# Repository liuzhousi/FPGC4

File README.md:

# FPGC4

[Project Wiki](https://www.b4rt.nl/fpgc4/)

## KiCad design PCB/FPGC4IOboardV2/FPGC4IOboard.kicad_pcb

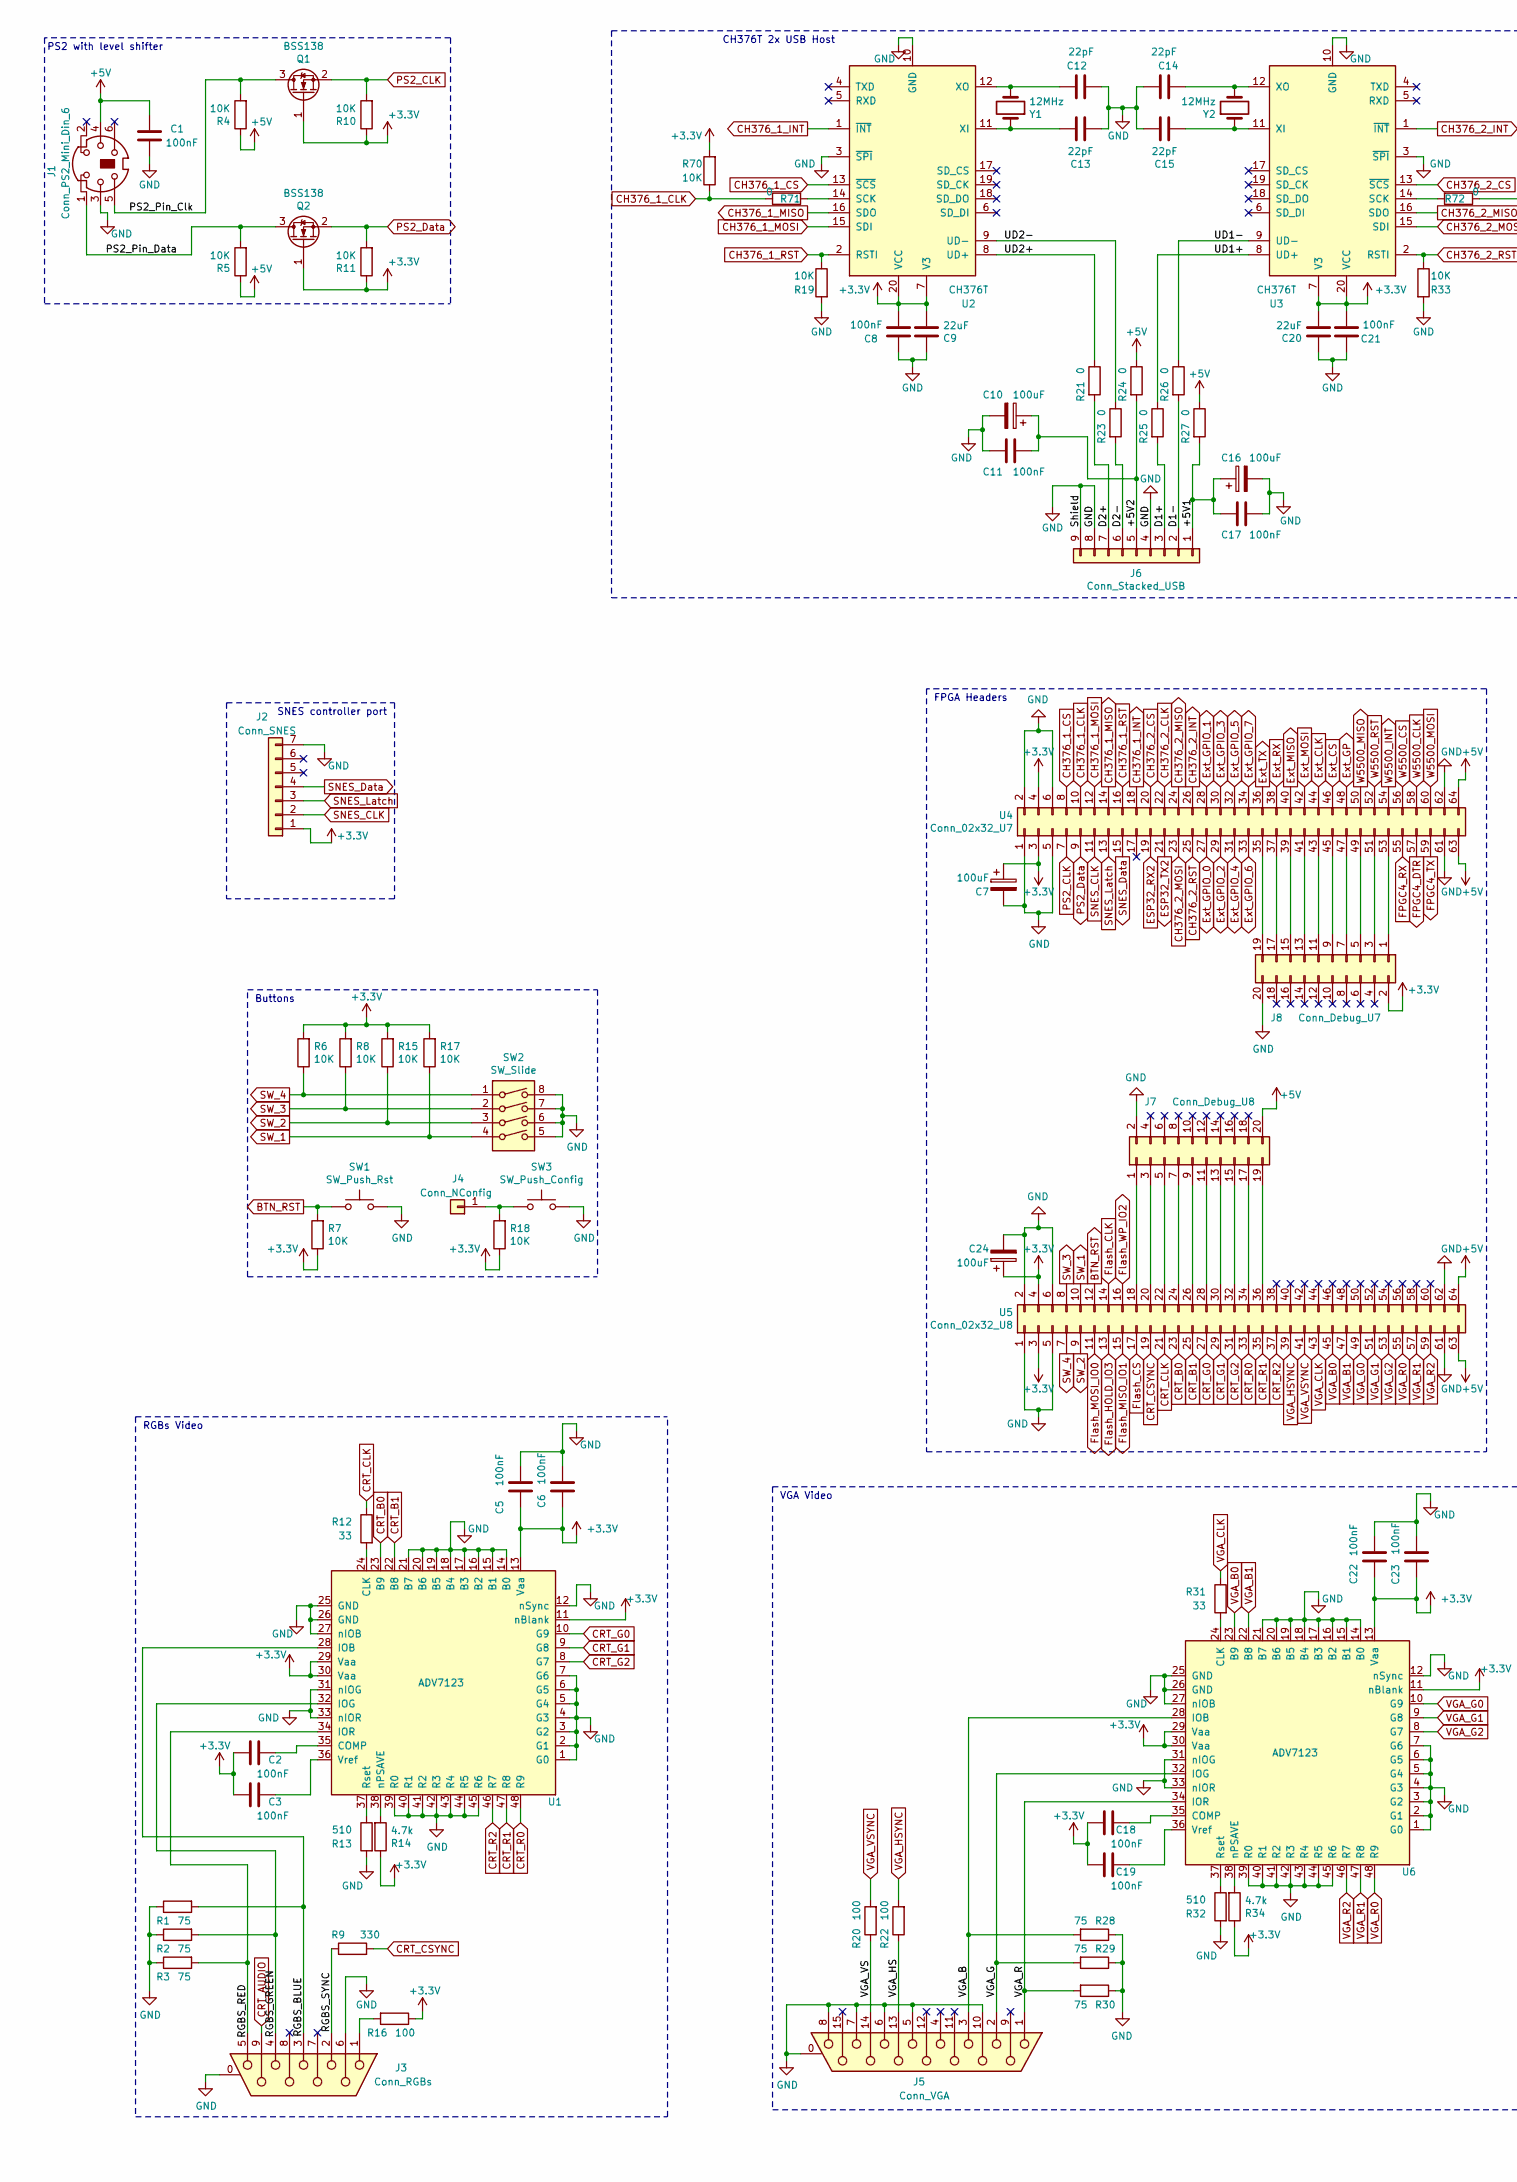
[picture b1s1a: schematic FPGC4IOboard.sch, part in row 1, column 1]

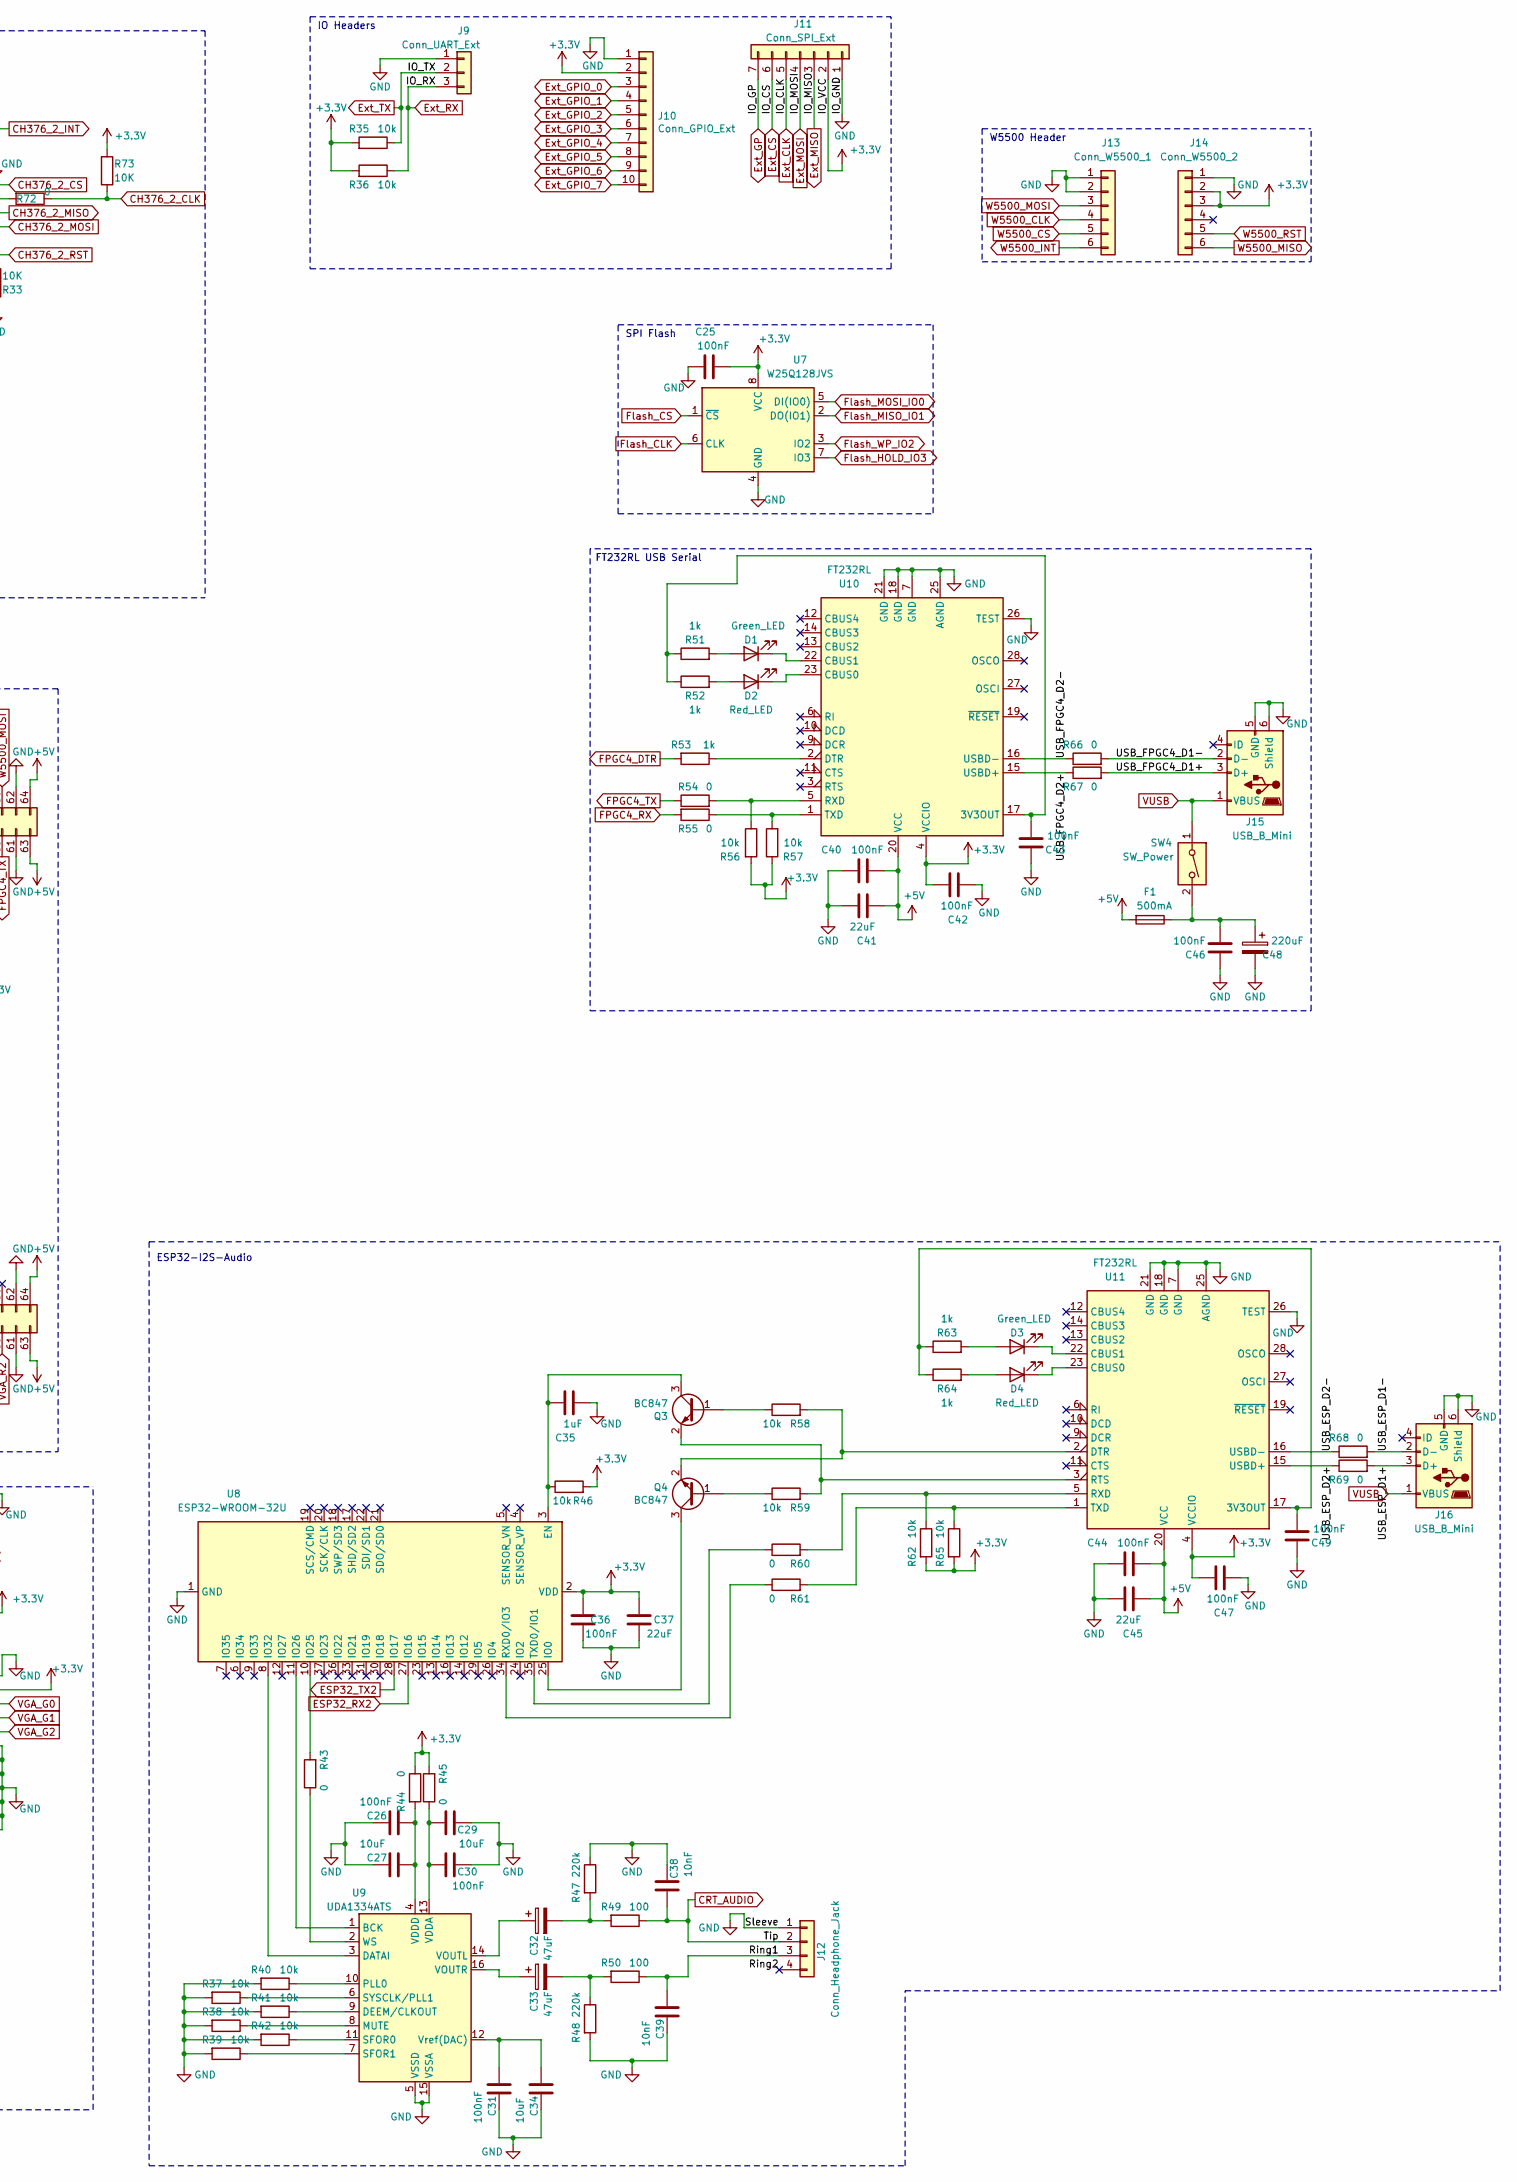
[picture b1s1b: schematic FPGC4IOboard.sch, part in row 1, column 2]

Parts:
C1, C2, C3, C5, C6, C8, C11, C17, C18, C19, C21, C22, C23, C25, C26, C30, C31, C36, C40, C42, C43, C44, C46, C47, C49: 100nF; C_0805_2012Metric_Pad1.15x1.40mm_HandSolder
C7, C10, C16, C24: 100uF; CP_Radial_D4.0mm_P2.00mm
C9, C20, C37, C41, C45: 22uF; C_0805_2012Metric_Pad1.15x1.40mm_HandSolder
C12, C13, C14, C15: 22pF; C_0805_2012Metric_Pad1.15x1.40mm_HandSolder
C27, C29, C34: 10uF; C_0805_2012Metric_Pad1.15x1.40mm_HandSolder
C32, C33: 47uF; CP_Radial_D4.0mm_P2.00mm
C35: 1uF; C_0805_2012Metric_Pad1.15x1.40mm_HandSolder
C38, C39: 10nF; C_0805_2012Metric_Pad1.15x1.40mm_HandSolder
C48: 220uF; CP_Radial_D5.0mm_P2.00mm
D1, D3: Green_LED; LED_0805_2012Metric_Pad1.15x1.40mm_HandSolder
D2, D4: Red_LED; LED_0805_2012Metric_Pad1.15x1.40mm_HandSolder
F1: 500mA; Fuse_1812_4532Metric_Pad1.30x3.40mm_HandSolder
J1: Conn_PS2_Mini_Din_6; Connector_Mini-DIN_Female_6Pin_2rows
J2: Conn_SNES; SNES_controller_port
J3: Conn_RGBs; DSUB9_CRT
J4: Conn_NConfig; PinHeader_1x01_P2.54mm_Vertical
J5: Conn_VGA; VGA_EDAC
J6: Conn_Stacked_USB; USB_A_Wuerth_61400826021_Horizontal_Stacked
J7: Conn_Debug_U8; PinHeader_2x10_P2.54mm_Vertical
J8: Conn_Debug_U7; PinHeader_2x10_P2.54mm_Vertical
J9: Conn_UART_Ext; PinSocket_1x03_P2.54mm_Vertical
J10: Conn_GPIO_Ext; PinSocket_1x10_P2.54mm_Vertical
J11: Conn_SPI_Ext; PinSocket_1x07_P2.54mm_Vertical
J12: Conn_Headphone_Jack; TRRS-PJ-320A
J13: Conn_W5500_1; PinSocket_1x06_P2.54mm_Vertical
J14: Conn_W5500_2; PinSocket_1x06_P2.54mm_Vertical
J15, J16: USB_B_Mini; USB_Mini-B_Lumberg_2486_01_Horizontal
Q1, Q2: BSS138; SOT-23
Q3, Q4: BC847; SOT-23
R1, R2, R3, R28, R29, R30: 75; R_0805_2012Metric_Pad1.15x1.40mm_HandSolder
R4, R5, R6, R7, R8, R10, R11, R15, R17, R18, R19, R33, R70, R73: 10K; R_0805_2012Metric_Pad1.15x1.40mm_HandSolder
R9: 330; R_0805_2012Metric_Pad1.15x1.40mm_HandSolder
R12, R31: 33; R_0805_2012Metric_Pad1.15x1.40mm_HandSolder
R13, R32: 510; R_0805_2012Metric_Pad1.15x1.40mm_HandSolder
R14, R34: 4.7k; R_0805_2012Metric_Pad1.15x1.40mm_HandSolder
R16, R20, R22, R49, R50: 100; R_0805_2012Metric_Pad1.15x1.40mm_HandSolder
R21, R23, R24, R25, R26, R27, R43, R44, R45, R54, R55, R60, R61, R66, R67, R68, R69, R71, R72: 0; R_0805_2012Metric_Pad1.15x1.40mm_HandSolder
R35, R36, R37, R38, R39, R40, R41, R42, R46, R56, R57, R58, R59, R62, R65: 10k; R_0805_2012Metric_Pad1.15x1.40mm_HandSolder
R47, R48: 220k; R_0805_2012Metric_Pad1.15x1.40mm_HandSolder
R51, R52, R53, R63, R64: 1k; R_0805_2012Metric_Pad1.15x1.40mm_HandSolder
SW1: SW_Push_Rst; SW_Tactile_SPST_Angled_PTS645Vx39-2LFS
SW2: SW_Slide; SW_DIP_SPSTx04_Slide_6.7x11.72mm_W8.61mm_P2.54mm_LowProfile
SW3: SW_Push_Config; SW_Tactile_SPST_Angled_PTS645Vx39-2LFS
SW4: SW_Power; switchAngled
U1, U6: ADV7123; LQFP-48_7x7mm_P0.5mm
U2, U3: CH376T; SSOP-20_5.3x7.2mm_P0.65mm
U4: Conn_02x32_U7; PinHeader_2x32_P2.54mm_Vertical
U5: Conn_02x32_U8; PinHeader_2x32_P2.54mm_Vertical
U7: W25Q128JVS; SOIC-8_5.23x5.23mm_P1.27mm
U8: ESP32-WROOM-32U
U9: UDA1334ATS; SSOP-16_4.4x5.2mm_P0.65mm
U10, U11: FT232RL; SSOP-28_5.3x10.2mm_P0.65mm
Y1, Y2: 12MHz; Crystal_HC49-4H_Vertical

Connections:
+3V3: C2.1, C3.1, C5.2, C6.1, C7.1, C8.2, C9.2, C18.1, C19.1, C20.2, C21.2, C22.2, C23.1, C24.1, C25.2, C36.2, C37.2, C42.2, C47.2, J2.1, J8.2, J10.2, J11.2, J14.2, J14.3, Q1.1 (G), Q2.1 (G), R6.2, R7.1, R8.2, R10.1, R11.1, R14.1, R15.2, R16.1, R17.2, R18.1, R34.1, R35.2, R36.2, R44.1, R45.2, R46.2, R56.2, R57.1, R62.2, R65.2, R70.2, R73.2, U1.11 (nBlank), U1.13 (Vaa), U1.29 (Vaa), U1.30 (Vaa), U2.7 (V3), U2.20 (VCC), U3.7 (V3), U3.20 (VCC), U4.3, U4.4, U5.3, U5.4, U6.11 (nBlank), U6.13 (Vaa), U6.29 (Vaa), U6.30 (Vaa), U7.8 (VCC), U8.2 (VDD), U10.4 (VCCIO), U11.4 (VCCIO)
+5V: C1.1, C40.2, C41.1, C44.2, C45.1, F1.2, J1.4, J7.20, R4.1, R5.1, R24.1, R27.1, U4.63, U4.64, U5.63, U5.64, U10.20 (VCC), U11.20 (VCC)
/+5V1: C16.1, C17.2, J6.1, R27.2
/+5V2: C10.1, C11.2, J6.5, R24.2
/D1+: J6.3, R25.2
/D1-: J6.2, R26.2
/D2+: J6.7, R21.2
/D2-: J6.6, R23.2
/PS2_Pin_Clk: J1.5, Q1.3 (D), R4.2
/PS2_Pin_Data: J1.1, Q2.3 (D), R5.2
/RGBS_BLUE: J3.3, R1.2, U1.28 (IOB)
/RGBS_GREEN: J3.4, R2.2, U1.32 (IOG)
/RGBS_RED: J3.5, R3.2, U1.34 (IOR)
/RGBS_SYNC: J3.2, R9.1
/Ring1: C39.1, J12.3, R50.1
/Ring2: J12.4
/UD1+: R25.1, U3.8 (UD+)
/UD1-: R26.1, U3.9 (UD-)
/UD2+: R21.1, U2.8 (UD+)
/UD2-: R23.1, U2.9 (UD-)
/USB_ESP_D1+: J16.3 (D+), R69.2
/USB_ESP_D1-: J16.2 (D-), R68.2
/USB_ESP_D2+: R69.1, U11.15 (USBD+)
/USB_ESP_D2-: R68.1, U11.16 (USBD-)
/USB_FPGC4_D1+: J15.3 (D+), R67.2
/USB_FPGC4_D1-: J15.2 (D-), R66.2
/USB_FPGC4_D2+: R67.1, U10.15 (USBD+)
/USB_FPGC4_D2-: R66.1, U10.16 (USBD-)
/VGA_B: J5.3, R28.2, U6.28 (IOB)
/VGA_G: J5.2, R29.2, U6.32 (IOG)
/VGA_HS: J5.13, R22.1
/VGA_R: J5.1, R30.2, U6.34 (IOR)
/VGA_VS: J5.14, R20.1
BTN_RST: R7.2, SW1.1, U5.12
CH376_1_CLK: R70.1, R71.1, U4.10
CH376_1_CS: U2.13 (~SCS), U4.8
CH376_1_INT: U2.1 (~INT~), U4.18
CH376_1_MISO: U2.16 (SDO), U4.14
CH376_1_MOSI: U2.15 (SDI), U4.12
CH376_1_RST: R19.1, U2.2 (RSTI), U4.16
CH376_2_CLK: R72.1, R73.1, U4.22
CH376_2_CS: U3.13 (~SCS), U4.20
CH376_2_INT: U3.1 (~INT~), U4.26
CH376_2_MISO: U3.16 (SDO), U4.24
CH376_2_MOSI: U3.15 (SDI), U4.23
CH376_2_RST: R33.1, U3.2 (RSTI), U4.25
CRT_AUDIO: C38.1, J3.9, J12.2, R49.1
CRT_B0: U1.23 (B9), U5.23
CRT_B1: U1.22 (B8), U5.25
CRT_CLK: R12.1, U5.21
CRT_CSYNC: R9.2, U5.19
CRT_G0: U1.10 (G9), U5.27
CRT_G1: U1.9 (G8), U5.29
CRT_G2: U1.8 (G7), U5.31
CRT_R0: U1.48 (R9), U5.33
CRT_R1: U1.47 (R8), U5.35
CRT_R2: U1.46 (R7), U5.37
ESP32_RX2: U4.19, U8.27 (IO16)
ESP32_TX2: U4.21, U8.28 (IO17)
Ext_CLK: J11.5, U4.44
Ext_CS: J11.6, U4.46
Ext_GP: J11.7, U4.48
Ext_GPIO_0: J10.3, U4.27
Ext_GPIO_1: J10.4, U4.28
Ext_GPIO_2: J10.5, U4.29
Ext_GPIO_3: J10.6, U4.30
Ext_GPIO_4: J10.7, U4.31
Ext_GPIO_5: J10.8, U4.32
Ext_GPIO_6: J10.9, U4.33
Ext_GPIO_7: J10.10, U4.34
Ext_MISO: J11.3, U4.40
Ext_MOSI: J11.4, U4.42
Ext_RX: J9.3, R36.1, U4.38
Ext_TX: J9.2, R35.1, U4.36
FPGC4_DTR: R53.2, U4.57
FPGC4_RX: R55.2, U4.55
FPGC4_TX: R54.1, U4.59
Flash_CLK: U5.14, U7.6 (CLK)
Flash_CS: U5.17, U7.1 (~CS)
Flash_HOLD_IO3: U5.13, U7.7 (IO3)
Flash_MISO_IO1: U5.15, U7.2 (DO(IO1))
Flash_MOSI_IO0: U5.11, U7.5 (DI(IO0))
Flash_WP_IO2: U5.16, U7.3 (IO2)
GND: C1.2, C5.1, C6.2, C7.2, C8.1, C9.1, C10.2, C11.1, C12.2, C13.1, C14.2, C15.1, C16.2, C17.1, C20.1, C21.1, C22.1, C23.2, C24.2, C25.1, C26.2, C27.2, C29.2, C30.2, C31.2, C34.2, C35.2, C36.1, C37.1, C38.2, C39.2, C40.1, C41.2, C42.1, C43.1, C44.1, C45.2, C46.1, C47.1, C48.2, C49.1, J1.3, J2.7, J3.0 (PAD), J3.6, J5.0 (PAD), J5.5, J5.6, J5.7, J5.8, J5.10, J6.4, J6.8, J6.9, J7.2, J8.20, J9.1, J10.1, J11.1, J12.1, J13.1, J13.2, J14.1, J15.5 (GND), J15.6 (Shield), J16.5 (GND), J16.6 (Shield), R1.1, R2.1, R3.1, R13.2, R19.2, R28.1, R29.1, R30.1, R32.2, R33.2, R37.2, R38.2, R39.2, R40.2, R41.2, R42.2, R47.1, R48.2, SW1.2, SW2.5, SW2.6, SW2.7, SW2.8, SW3.2, U1.1 (G0), U1.2 (G1), U1.3 (G2), U1.4 (G3), U1.5 (G4), U1.6 (G5), U1.7 (G6), U1.12 (nSync), U1.14 (B0), U1.15 (B1), U1.16 (B2), U1.17 (B3), U1.18 (B4), U1.19 (B5), U1.20 (B6), U1.21 (B7), U1.25 (GND), U1.26 (GND), U1.27 (nIOB), U1.31 (nIOG), U1.33 (nIOR), U1.39 (R0), U1.40 (R1), U1.41 (R2), U1.42 (R3), U1.43 (R4), U1.44 (R5), U1.45 (R6), U2.3 (~SPI~), U2.10 (GND), U3.3 (~SPI~), U3.10 (GND), U4.1, U4.2, U4.5, U4.6, U4.61, U4.62, U5.1, U5.2, U5.5, U5.6, U5.61, U5.62, U6.1 (G0), U6.2 (G1), U6.3 (G2), U6.4 (G3), U6.5 (G4), U6.6 (G5), U6.7 (G6), U6.12 (nSync), U6.14 (B0), U6.15 (B1), U6.16 (B2), U6.17 (B3), U6.18 (B4), U6.19 (B5), U6.20 (B6), U6.21 (B7), U6.25 (GND), U6.26 (GND), U6.27 (nIOB), U6.31 (nIOG), U6.33 (nIOR), U6.39 (R0), U6.40 (R1), U6.41 (R2), U6.42 (R3), U6.43 (R4), U6.44 (R5), U6.45 (R6), U7.4 (GND), U8.1 (GND), U8.15 (GND), U8.38 (GND), U8.39 (GND), U9.5 (VSSD), U9.15 (VSSA), U10.7 (GND), U10.18 (GND), U10.21 (GND), U10.25 (AGND), U10.26 (TEST), U11.7 (GND), U11.18 (GND), U11.21 (GND), U11.25 (AGND), U11.26 (TEST)
unnamed: C2.2, U1.35 (COMP)
unnamed: C3.2, U1.36 (Vref)
unnamed: C12.1, U2.12 (XO), Y1.2
unnamed: C13.2, U2.11 (XI), Y1.1
unnamed: C14.1, U3.12 (XO), Y2.2
unnamed: C15.2, U3.11 (XI), Y2.1
unnamed: C18.2, U6.35 (COMP)
unnamed: C19.2, U6.36 (Vref)
unnamed: C26.1, C27.1, R44.2, U9.4 (VDDD)
unnamed: C29.1, C30.1, R45.1, U9.13 (VDDA)
unnamed: C31.1, C34.1, U9.12 (Vref(DAC))
unnamed: C32.1, U9.14 (VOUTL)
unnamed: C32.2, R47.2, R49.2
unnamed: C33.1, U9.16 (VOUTR)
unnamed: C33.2, R48.1, R50.2
unnamed: C35.1, Q3.3 (C), R46.1, U8.3 (EN)
unnamed: C43.2, R51.1, R52.1, U10.17 (3V3OUT)
unnamed: C46.2, C48.1, F1.1, SW4.2
unnamed: C49.2, R63.1, R64.1, U11.17 (3V3OUT)
unnamed: D1.1 (K), U10.22 (CBUS1)
unnamed: D1.2 (A), R51.2
unnamed: D2.1 (K), U10.23 (CBUS0)
unnamed: D2.2 (A), R52.2
unnamed: D3.1 (K), U11.22 (CBUS1)
unnamed: D3.2 (A), R63.2
unnamed: D4.1 (K), U11.23 (CBUS0)
unnamed: D4.2 (A), R64.2
unnamed: J3.1, R16.2
unnamed: J4.1, R18.2, SW3.1
unnamed: J7.1, U5.18
unnamed: J7.3, U5.20
unnamed: J7.5, U5.22
unnamed: J7.7, U5.24
unnamed: J7.9, U5.26
unnamed: J7.11, U5.28
unnamed: J7.13, U5.30
unnamed: J7.15, U5.32
unnamed: J7.17, U5.34
unnamed: J7.19, U5.36
unnamed: J8.1, U4.53
unnamed: J8.3, U4.51
unnamed: J8.5, U4.49
unnamed: J8.7, U4.47
unnamed: J8.9, U4.45
unnamed: J8.11, U4.43
unnamed: J8.13, U4.41
unnamed: J8.15, U4.39
unnamed: J8.17, U4.37
unnamed: J8.19, U4.35
unnamed: Q3.1 (B), R58.1
unnamed: Q3.2 (E), R59.2, U11.3 (RTS)
unnamed: Q4.1 (B), R59.1
unnamed: Q4.2 (E), R58.2, U11.2 (DTR)
unnamed: Q4.3 (C), U8.25 (IO0)
unnamed: R12.2, U1.24 (CLK)
unnamed: R13.1, U1.37 (Rset)
unnamed: R14.2, U1.38 (nPSAVE)
unnamed: R31.2, U6.24 (CLK)
unnamed: R32.1, U6.37 (Rset)
unnamed: R34.2, U6.38 (nPSAVE)
unnamed: R37.1, U9.6 (SYSCLK/PLL1)
unnamed: R38.1, U9.8 (MUTE)
unnamed: R39.1, U9.7 (SFOR1)
unnamed: R40.1, U9.10 (PLL0)
unnamed: R41.1, U9.9 (DEEM/CLKOUT)
unnamed: R42.1, U9.11 (SFOR0)
unnamed: R43.1, U9.2 (WS)
unnamed: R43.2, U8.10 (IO25)
unnamed: R53.1, U10.2 (DTR)
unnamed: R54.2, R56.1, U10.5 (RXD)
unnamed: R55.1, R57.2, U10.1 (TXD)
unnamed: R60.1, U8.35 (TXD0/IO1)
unnamed: R60.2, R62.1, U11.5 (RXD)
unnamed: R61.1, U8.34 (RXD0/IO3)
unnamed: R61.2, R65.1, U11.1 (TXD)
unnamed: R71.2, U2.14 (SCK)
unnamed: R72.2, U3.14 (SCK)
unnamed: U8.8 (IO32), U9.3 (DATAI)
unnamed: U8.11 (IO26), U9.1 (BCK)
PS2_CLK: Q1.2 (S), R10.2, U4.7
PS2_Data: Q2.2 (S), R11.2, U4.9
SNES_CLK: J2.2, U4.11
SNES_Data: J2.4, U4.15
SNES_Latch: J2.3, U4.13
SW_1: R17.1, SW2.4, U5.10
SW_2: R15.1, SW2.3, U5.9
SW_3: R8.1, SW2.2, U5.8
SW_4: R6.1, SW2.1, U5.7
VGA_B0: U5.45, U6.23 (B9)
VGA_B1: U5.47, U6.22 (B8)
VGA_CLK: R31.1, U5.43
VGA_G0: U5.49, U6.10 (G9)
VGA_G1: U5.51, U6.9 (G8)
VGA_G2: U5.53, U6.8 (G7)
VGA_HSYNC: R22.2, U5.39
VGA_R0: U5.55, U6.48 (R9)
VGA_R1: U5.57, U6.47 (R8)
VGA_R2: U5.59, U6.46 (R7)
VGA_VSYNC: R20.2, U5.41
VUSB: J15.1 (VBUS), J16.1 (VBUS), SW4.1
W5500_CLK: J13.4, U4.58
W5500_CS: J13.5, U4.56
W5500_INT: J13.6, U4.54
W5500_MISO: J14.6, U4.50
W5500_MOSI: J13.3, U4.60
W5500_RST: J14.5, U4.52

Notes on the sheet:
FT232RL USB Serial
IO Headers
SNES controller port
PS2 with level shifter
CH376T 2x USB Host
RGBs Video
VGA Video
ESP32-I2S-Audio
SPI Flash
W5500 Header
Buttons
FPGA Headers

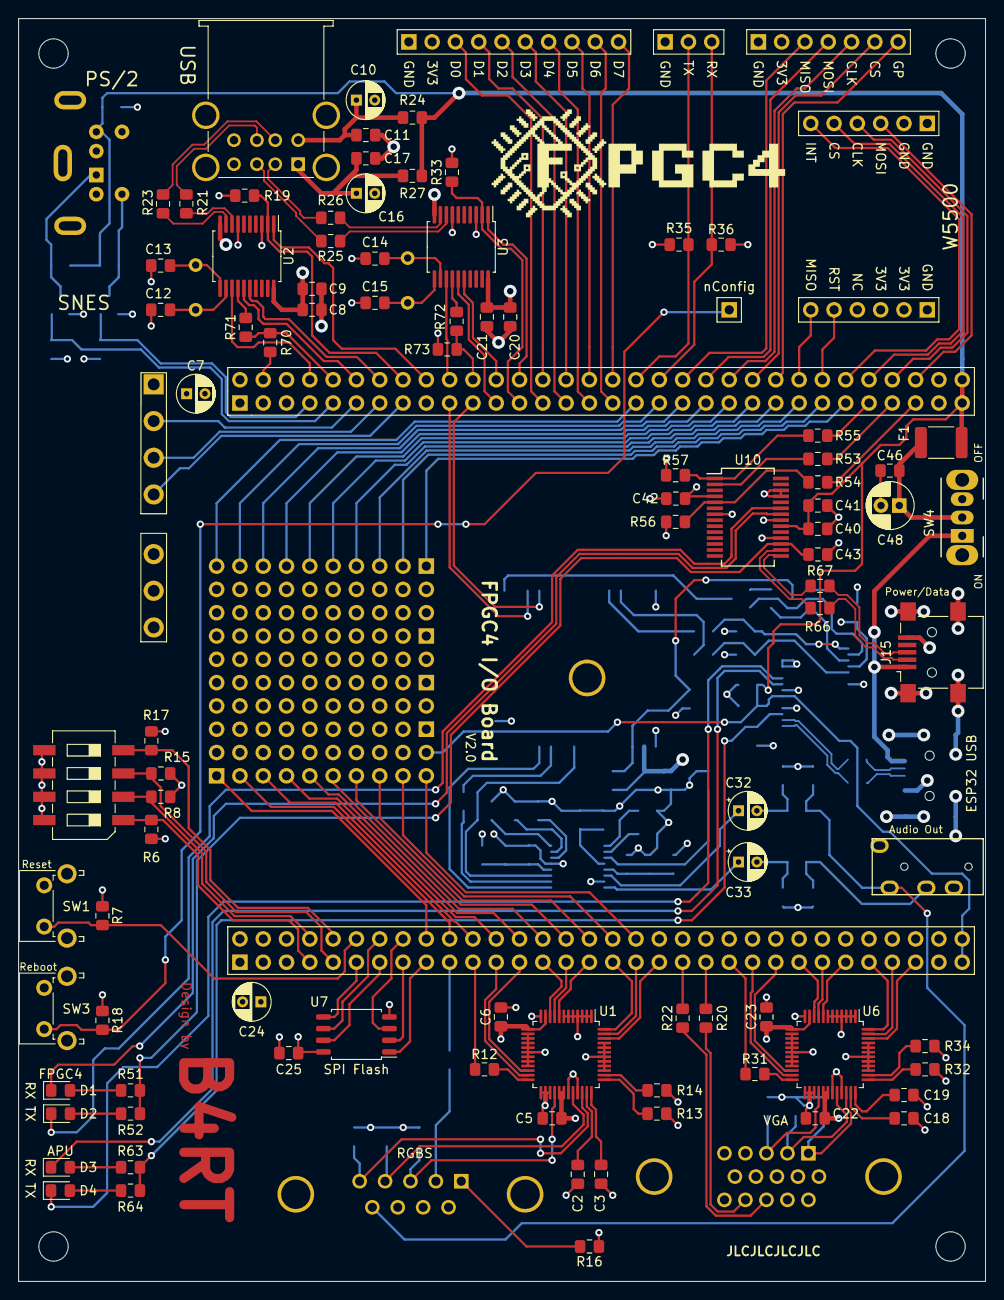
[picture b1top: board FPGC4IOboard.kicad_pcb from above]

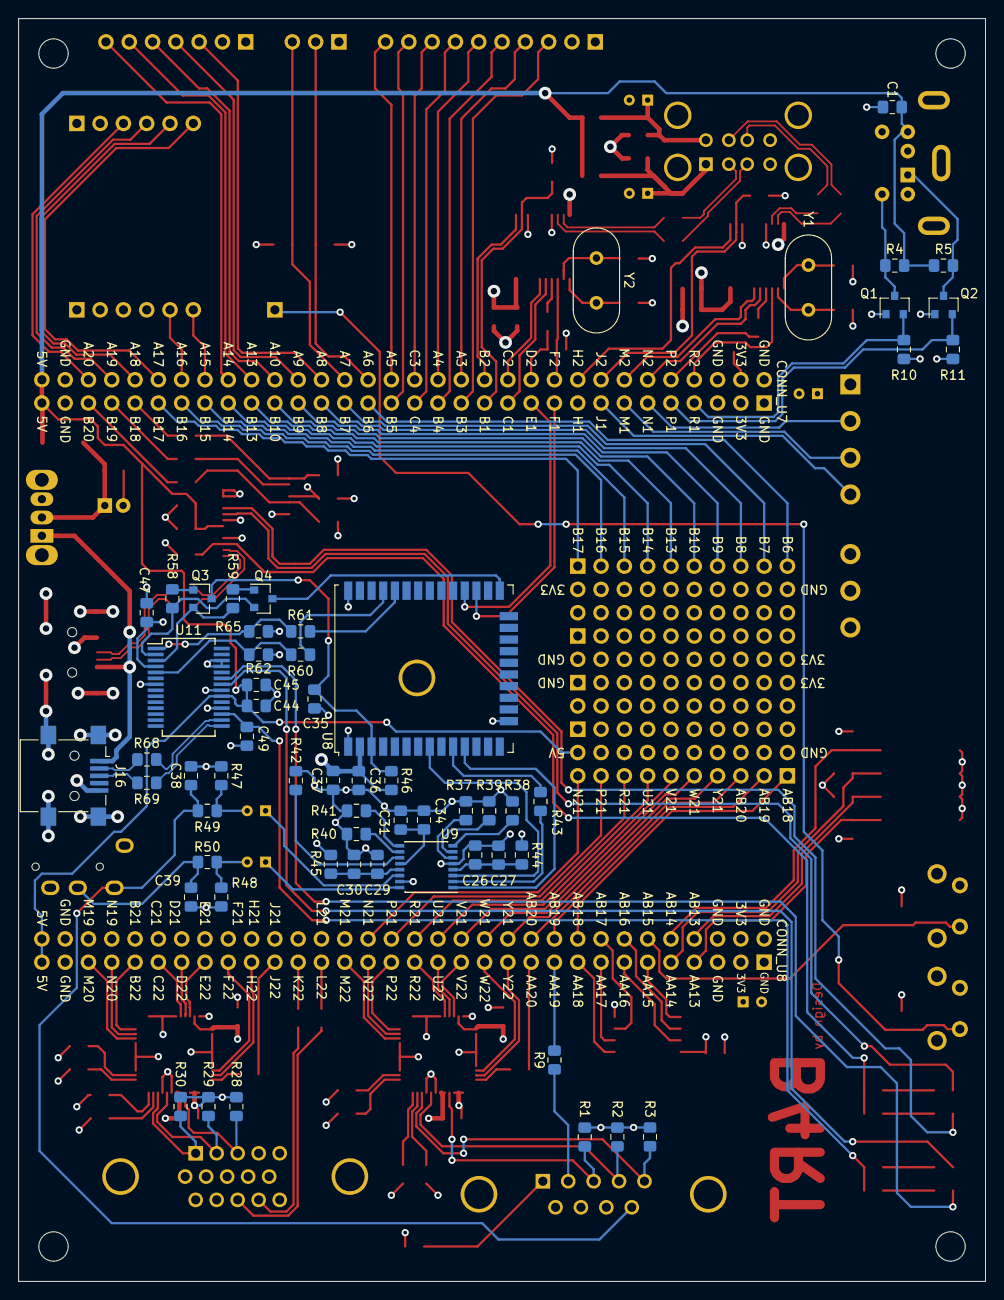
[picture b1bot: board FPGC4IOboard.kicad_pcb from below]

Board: 4 copper layers, 105.4 x 137.7 mm, 163 parts (59 on the bottom side), 189 nets.

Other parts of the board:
LOGO: LOGO

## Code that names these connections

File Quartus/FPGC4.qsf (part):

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set_location_assignment PIN_W1 -to SDRAM_A[10]
set_location_assignment PIN_Y4 -to SDRAM_A[11]
set_location_assignment PIN_V6 -to SDRAM_A[12]
set_location_assignment PIN_AA20 -to crt_clk
set_location_assignment PIN_AA19 -to crt_sync
set_location_assignment PIN_M22 -to crt_r[2]
set_location_assignment PIN_N22 -to crt_r[1]
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set_location_assignment PIN_V22 -to crt_g[0]
set_location_assignment PIN_W22 -to crt_b[1]
set_location_assignment PIN_Y22 -to crt_b[0]
set_location_assignment PIN_J22 -to vga_clk
set_location_assignment PIN_L22 -to vga_hs
set_location_assignment PIN_K22 -to vga_vs
set_location_assignment PIN_M20 -to vga_r[2]
set_location_assignment PIN_N20 -to vga_r[1]
set_location_assignment PIN_B22 -to vga_r[0]
set_location_assignment PIN_C22 -to vga_g[2]
set_location_assignment PIN_D22 -to vga_g[1]
set_location_assignment PIN_E22 -to vga_g[0]
set_location_assignment PIN_F22 -to vga_b[1]
set_location_assignment PIN_H22 -to vga_b[0]
set_location_assignment PIN_B19 -to UART0_dtr
set_location_assignment PIN_B20 -to UART0_out
set_location_assignment PIN_B18 -to UART0_in
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set_location_assignment PIN_C2 -to SPI2_miso
set_location_assignment PIN_B1 -to SPI2_rst
set_location_assignment PIN_B2 -to SPI2_nint
set_location_assignment PIN_P1 -to PS2_data
set_location_assignment PIN_R1 -to PS2_clk
set_location_assignment PIN_N1 -to SNES_clk
set_location_assignment PIN_M1 -to SNES_latch
set_location_assignment PIN_J1 -to SNES_data
set_location_assignment PIN_A18 -to SPI3_cs
set_location_assignment PIN_A19 -to SPI3_clk
set_location_assignment PIN_A20 -to SPI3_mosi
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
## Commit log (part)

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2019-11-21 Added empty quartus project, added empty-ish verilog files, copied init memory files from FPGC3
2019-11-23 Added and optimized FSX. Still need to replace linebuffers with Dual Port RAM
2019-12-04 Started creating memory controller that handles SPI and SDRAM reading. Still need to add VRAM, ROM and I/O. Also FSX has to be converted for 480x272 display
2019-12-07 First CPU version. Fixed FSX for 480x272 display. Semi tested in Quartus. Need to make assembler to fully test CPU.
2019-12-08 Assembler and Programmer added. First bootloader test successful
2019-12-10 Created documentation
2019-12-12 Started graphics library to test CPU. Fixed bug in bgt bge instructions where flag checks were incorrect
2019-12-12 Added some quartus files to gitignore
2019-12-12 Moved gitignore from assembler folder to main gaitignore. Added the two main quartus output files, fixed gitignore for that folder. modified checklist.txt
2019-12-13 Added copy of build files for Sublime Text 3. Fixed assembly compile script to stop when an error is ofund (when the exit code is not 0)
2019-12-13 Added .ds instruction for text strings. Added bootloader code to readme. Fixed missing space in branch instruction assembly process. Made default vram empty, verified on FPGA.
2019-12-13 Improved regbank to use M9K blocks
2019-12-13 Added keyboard and SNES I/O
2019-12-15 Big reimplementation of GPU. Now has scrolling BG support and a non scrolling window table. Memory map adjusted, just as the hardcoded jump address in the bootloader. Also probably fixed a bug where 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
2019-12-17 Added three CTC timers and two tone generators. Really need to update the readme with new memory map, audio and FSX2 infogit status!
2019-12-22 Added UART and a program to write code directly via UART
2019-12-24 Added UARTbootloader option, added GPIO back, fixed reset, bootloader works in both normal (10sec) and UART mode (~0sec). Discovered bug: Window color addresses have problems with scrolling
2019-12-28 Added SPI module for CH376S. Also started with coding for CH376S. Will/must eventually add 'library' support for assembler.
2019-12-29 Improved CH376 library. Added read (unfinished) and write functions.
2019-12-30 Added library support for the assembler. Created some libraries (GFX, UART, SPI, CH376, STD). Still need to do music library. Moving big data blocks to seperate asm files also works. Recursive librar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
2020-01-09 Updated README a bit
2020-01-10 Implemented sprites for single sprites. Big challenge now in adding more sprites in a modular way
2020-01-10 Further improvements in multiple sprite rendering
2020-01-11 Sprite rendering now works for 16 sprites (tested in hardware). Possible oppertunity for creating a sprite selector during the visible part of each line to increase this number to 64 or 128.
2020-01-16 Changed video output to 320x240 for RGBs primarily on CRT TVs. Fixed palette scroll bug in background and window renderer (this module should now be perfectly working). However, multiple new bugs cur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
2020-01-16 Fixed all bugs in sprite renderer. As far as I know all bugs in the FSX2 are fixed now, and all basic features are implemented. Should make a test program/game that utilizes most/all FSX2 features to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
2020-01-18 Updated documentation. Fixed small bug in flash.sh where a hardcoded filename was used
2020-01-21 Improved tile and color converters. Sorting tiles on brightness, started creating the test level design for platformer game
2020-01-22 Improved color in scripts, added load32 macro and replaces old load/loadhi combos in libraries with it. Improved MidiConverter to accept (and truncate) midis with more than 4 notes at the same time. 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
2020-01-24 Fixed CRT timings. Removed old checklist file. Removed old things from CH376Snotes file
2020-04-04 Updated README with a better project introduction
2020-04-04 Added history of project to README
2020-04-05 Improved README, added table of contents. Slightly changed timings of PLL for the GPU. Changed settings to multiplication and division, to circumvent a bug in Quartus
2020-04-10 Adjusted FPGA pinout to PCB. Small update in README
2020-04-15 Changed default bootloader mode to UART (made an update about this in the README as well). Changed the CRT color bit order in the Quartus assignments. Changed uartFlasher to use /dev/ttyUSB0 by defau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
2020-04-15 Tried to add pictures to README, also added confirmation that Winbond SDRAM is 100% compatible
2020-04-15 Fixed typos in README
2020-04-16 Added more KiCad info in README. Also updated README with quite some things
2020-05-04 Prepared simulation for interrupt extender module. Also edited some test code
2020-05-05 Reimplemented CTCtimer (is now OStimer). Verified in verilog. Still needs to be imlemented in Quartus and tested in hardware.
2020-05-05 Added and partially tested new interrupts and timers (only timers are tested now) in hardware after merging the changes to the quartus files
2020-05-06 Changed PS/2 module to only read scan codes and throw an interrupt so the rest can be done in software.
2020-05-14 Created documentation site. Replaced readme with link to hosted documentation site
2020-05-15 Minor fixes to documentation
2020-05-16 Created run and deploy scripts for documentation. Added new pages to documentation and edited some (mostly specs and index)
2020-05-20 Added logo to readme with link to documentation website/wiki
2020-05-20 Added basically working C to B332 asm compiler. Many improvements have to be made to it, but the basics work.
2020-05-20 Added Licence
2020-05-20 Added bitwise AND, OR and XOR to Ccompiler
2020-05-21 Added and verified DTR UART reset in simulation and hardware. Also updated documentation a bit (still behind).
2020-05-21 Created and improved several build and test scripts for compiling and sending code to FPGC4. Big thing of commit is now having runCfiles.sh which returns the return code for the .c file argument when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
2020-06-09 Possile fix for edge case in substraction
2020-06-10 Added inline assembly support. Also added a test for it.
2020-06-10 Added support for double/circulair includes. Improved test for this.
2020-06-11 Successfully implemented itoa using (very inefficient) division and modulus.
2020-06-12 updated documentation on C compiler
2020-06-16 Fixed ReadAt bug, probably is still present in SetAt, though I currently do not have a test case for that. Having issues with the serial monitor not working/FPGC4 not working. Will need to investigat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
2020-07-04 Moved from Ubuntu to WSL2. Added Windows version of UART flasher, since WSL2 cannot access (yet?) usb/serial devices. Updated to newer version of Quartus in Windows. Still need to test new build in h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
2020-07-05 Added USB MIDI synthesizer code
2020-07-05 Added labels to global variables for consistency (and fixing errors). Global arrays cannot be indexed yet with variables. Current workaround is creating a pointer and adding the index to the pointer 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
2020-07-05 Cleaned/optimized midi.c code a bit
2020-07-08 Improved Serial Monitor (win version for WSL2). Keyboard interrupt works properly now (removing the need to physically press the reset button to force a byte over UART), and it does not hog up the CP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
2020-07-09 Added CH376 (stabilized) interrupt to memory map. Improved midi.c with interrupt during wait. Changed asm build script to work under WSL2. Quickly updated documentation about new interrupt in memory 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
2020-07-10 Improved CH376 Library. Fixed issues (afaik) with SET IL in Ccompiler
2020-07-10 Fixed problem in Ccompiler where the count of a MemSpot of a target spot is a RegSpot instead of a LiteralSpot. Problem is fixed by adding a series of instructions to properly calculate the memory ad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
2020-07-13 Added ESP32 Synthesizer project. Changed pins of UART2 (for communication with ESP32Synth) to the two debug pins it currently is attached to in hardware (pin V21 and W21)
2020-07-13 Updated Documentation a bit (with new APU and small other things here and there)
2020-07-26 Migrated from WSL2 to WSL1. Fixed some uart flasher related things (can run from wsl1 directly, and fixed some thread terminating issues). Fixed some warnings from python. Tested loading project dire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
2020-08-10 Added W5500 web server code. Added SPI2 (GP) in hardware. Changed some static paths to relative ones within Quartus project.
2020-08-11 Added/improved webserver, now using CH376 for webserver files. Improved CH376 library.
2020-08-13 Improved CH376 read and write functions. General improvements to that library, like error handling using return values. Small changes to documentation about 8.3 filenames and todo
2020-08-25 Enabled VGA output, using the same timings as the CRT output. Made asm buildscript executable
2020-08-26 VGA 240p now works perfectly on my monitor. Added nreset in Quartus. Updated midi converter for new ESP32Synth, and made a simple test rom in assembly to verify that midi playback works perfectly now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
2020-08-28 Added new midi player to midiSynth.c
2020-09-01 updated buildscript for simulation. updated libTest.c with timer test code. reduced timeout of runTests.sh to 0.1 second. changed uart port to ttyUSB0 (since I'm running on native Linux now). removed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
2020-09-02 removed old midiconverter script. Set maximum velocity to 80 in converter script to allow for playing along. Made converscript executable
2020-09-02 changed fix to add NOP between double label from Ccompiler to Assembler, reducing the number of NOPs in compiled C code
2020-09-04 Updated documentation. Reimplemented SPI module. Now uses 6.25MHz clock.
2020-09-04 Updated specs list in documentation
2020-09-10 Simplified synchronizer, made frameDrawn a register, added synchronizer registers as synchronizer registers in quartus. Fixes timing requirement errors
2020-09-12 Improved bootloader by adding UART bootloader in ROM, removing the need for a valid program in the SPI flash to boot. This allows for an SPI flash programmer to be implemented (after allowing writes 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
2020-09-13 New bootloader: now prints logo as post. Bootloader is recompiled from scratch, with manual adjustments made to certain addresses. Does not clear vram beforehand. Might add that later in the 36 lines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
2020-09-13 Updated documentation on new bootloader with POST/logo, removing summary of compiled bootloader binary because size. Removed a few old files that are no longer useful.
2020-09-19 Started with SPI flash programmer using FPGC4 as programmer. Updated documentation on FPGA utilization
2020-09-19 Back to WSL2 since my laptop came back from repair and WSL2 is now included in the non-insider builds of Windows 10
2020-10-24 Added PCB V2 project (almost finished). Added some 3d models to a folder. Attemped to properly reoptimize Ccompiler, though it is not stable yet and previous programs mostly do not work anymore now (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
2020-11-04 Fixed Ccompiler issue where the count of a memspot was a register. This case is quite common when a variable is used as the index of an array.
2020-11-05 Tested new Ccompiler some more. It appears to work just fine. Had issue with new USB flash drive: CH376 requires the drive to be formatted in a certain way
2020-11-06 Updated documentation a bit
2020-11-07 Updated kicad paths for linux
2020-11-07 Worked on FPGC4 flash programmer, can do reads, writes and erases now. Modified C build scripts for Linux, ran simulation so I can make a screenshot later for in the documentation.
2020-11-08 Added SPI flasher using FPGC4 as programmer
2020-11-08 Applied gitignore on tmp files in Programmer directory
2020-11-10 Improved documentation a bit
2020-11-11 Cleaned up ALU and Control Unit Verilog code. Added random ideas section in progress.md
2020-11-16 Removed Arduino based SPI flash programmer. Updated documentation for new SPI flash programmer
2020-11-19 New memory map, updated hardware and bootloaders for new memory map. New stabilizer/synchronizer design by using a single big module at the top level. Still a lot to test, still a lot of code to upda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
2020-12-05 Improved testbench, changed addresses in stdlib.h, removed Stabilizer.v

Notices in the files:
Quartus/FPGC4.qsf:
Copyright (C) 1991-2012 Altera Corporation
